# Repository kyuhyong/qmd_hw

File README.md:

# Q_Motor_Driver_hw

A stackable BLDC motor controller board based and compatible with Odrive project (https://github.com/madcowswe/ODriveHardware).

Part of this project is based from azmat's single channel BLDC controller board (https://github.com/azmat-bilal/bldc_motor_controller_pcb.git)

## Introduction

This project includes 3 PCB boards as Main Board(MB), M0 Board(M0B) and M1 Board(M1B). 

- MB : Main controller, USB, CAN interface

- M0B : Gate driver for M0, 5V power supply for MB
- M1B : Gate driver for M1

MB is in between M0B and M1B which are connected by 2mm pitch socket and header. 

If only 1 axis needed the M1B can be removed. 

If more power is needed, simply redesign M0B or M1B with higher power FET's and put together with MB.

## Odrive compatibility

This project is supposed to be compatible with odrive v3.6-56V.

<div align="center">
  
</div>

## Announcement

This project is still in development and need modification to be working as expected.

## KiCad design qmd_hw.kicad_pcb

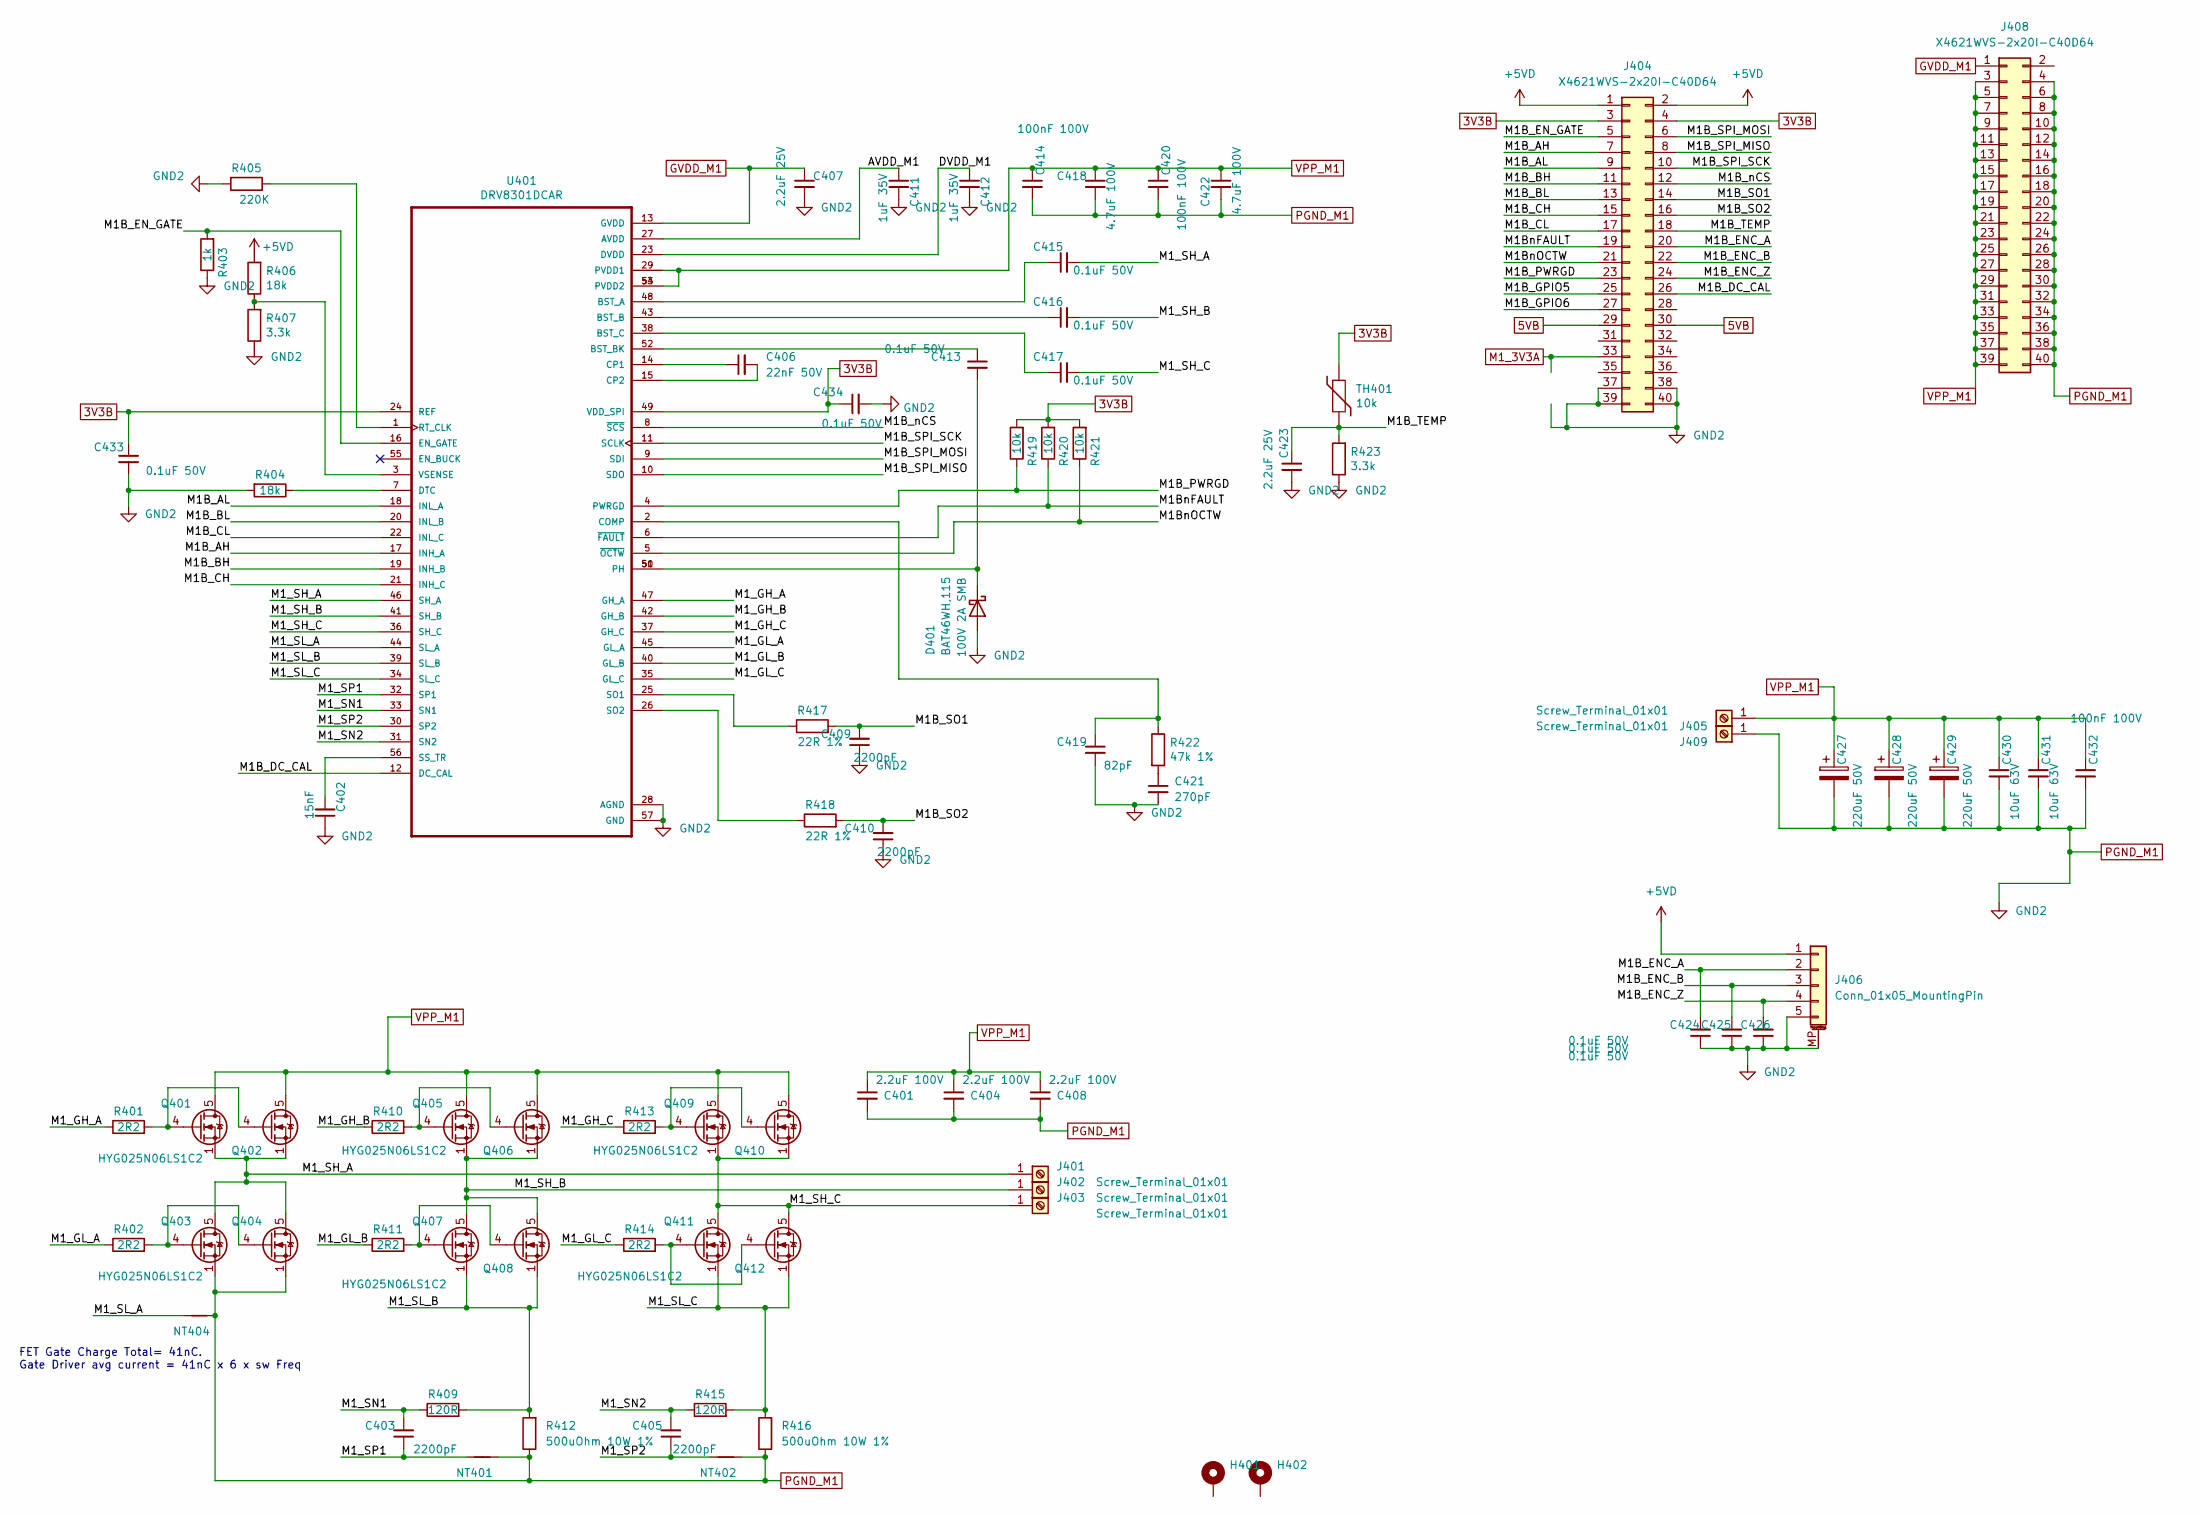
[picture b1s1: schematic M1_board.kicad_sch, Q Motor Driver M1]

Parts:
C401, C404, C408: 2.2uF 100V; C_1210_3225Metric; MPN HMK325B7225KN-T; JLCPN C92775
C402: 15nF; C_0402_1005Metric; MPN GCM155R71E153JA55D
C403, C405, C409, C410: 2200pF; C_0402_1005Metric; MPN CL05B222KB5NNNC; JLCPN C84703
C406: 22nF 50V; C_0402_1005Metric; MPN CL05B223KB5VPNC; JLCPN C307335
C407, C423: 2.2uF 25V; C_0603_1608Metric; MPN CL10A225KB8NNNC; JLCPN C913904
C411, C412: 1uF 35V; C_0603_1608Metric; MPN CL05A105KL5NRNC; JLCPN C307413
C413, C415, C416, C417, C434: 0.1uF 50V; C_0402_1005Metric
C414, C420, C432: 100nF 100V; C_0402_1005Metric; MPN GRM155R62A104KE14D; JLCPN C162178
C418: 4.7uF 100V; C_1210_3225Metric; MPN HMK325C7475KMHPE; JLCPN C385986
C419: 82pF; C_0402_1005Metric; MPN C1005NP0820JGTS; JLCPN C147470
C421: 270pF; C_0603_1608Metric; MPN CGA2B2C0G1H271JT0Y0F; JLCPN C695156
C422: 4.7uF 100V; C_1210_3225Metric; MPN HMK325C7475KN-TE
C424, C425, C426, C433: 0.1uF 50V; C_0603_1608Metric; MPN CL10B104KB8NNNC; JLCPN C1591
C427, C428, C429: 220uF 50V; CP_Elec_10x14.3; MPN EEHZS1H221P; JLCPN C385885
C430, C431: 10uF 63V; C_1210_3225Metric; MPN CL32B106KMVNNWE
D401: 100V 2A SMB; D_SOD-123F; MPN BAT46WH,115; JLCPN C426768
H401: MountingHole_Pad; MountingHole_3.2mm_M3_ISO7380_Pad
H402: MountingHole_Pad; MountingHole_3.2mm_M3_ISO7380_Pad_TopBottom
J401, J402, J403, J405, J409: Screw_Terminal_01x01; SolderWire-2.5sqmm_1x01_D2.4mm_OD3.6mm
J404, J408: X4621WVS-2x20I-C40D64; PinHeader_2x20_P2.0mm_Vertical_SMD_877594051; MPN X4621WVS-2x20I-C40D64; JLCPN C2883178
J406: Conn_01x05_MountingPin; JST_PH_B5B-PH-SM4-TB_1x05-1MP_P2.00mm_Vertical; MPN B5B-PH-SM4-TB(LF)(SN); JLCPN C265085
NT401, NT402, NT404: Net-Tie_2; NetTie-2_SMD_Pad0.5mm
Q401, Q402, Q403, Q404, Q405, Q406, Q407, Q408, Q409, Q410, Q411, Q412: HYG025N06LS1C2; TDSON-8-1; MPN HYG025N06LS1C2
R401, R402, R410, R411, R413, R414: 2R2; R_0603_1608Metric; MPN RC0603FR-072R2L; JLCPN C98220
R403: 1k; R_0402_1005Metric; MPN ERJ-2RKF1001X
R404, R406: 18k; R_0402_1005Metric; MPN CRCW040218K0FKED
R405: 220K; R_0402_1005Metric; MPN CR0402-JW-224GLF; JLCPN C203142
R407, R423: 3.3k; R_0603_1608Metric; MPN RC0603JR-073K3L; JLCPN C114432
R409, R415: 120R; R_0603_1608Metric; MPN ERJ-2RKF1200X
R412, R416: 500uOhm 10W 1%; WSLP3921L5000FEA; MPN WSLP3921L5000FEA
R417, R418: 22R 1%; R_0402_1005Metric; MPN AC0402JR-0722RL; JLCPN C144722
R419, R420, R421: 10k; R_0603_1608Metric; MPN RC0603FR-0710KL
R422: 47k 1%; R_0402_1005Metric; MPN RC0402FR-0747KL; JLCPN C93943
TH401: 10k; R_0402_1005Metric; MPN CRCW040210K0FKEDC
U401: DRV8301DCAR; SOP50P810X120-57N; MPN DRV8301DCAR

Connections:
3V3B: C433.1, C434.1, J404.3, J404.4, R419.2, R420.2, R421.2, TH401.1, U401.24 (REF), U401.49 (VDD_SPI)
5VB: J404.29, J404.30
+5VD: J404.1, J404.2, J406.1, R406.2
/M1_board/AVDD_M1: C411.1, U401.27 (AVDD)
/M1_board/DVDD_M1: C412.1, U401.23 (DVDD)
/M1_board/M1B_AH: J404.7, U401.17 (INH_A)
/M1_board/M1B_AL: J404.9, U401.18 (INL_A)
/M1_board/M1B_BH: J404.11, U401.19 (INH_B)
/M1_board/M1B_BL: J404.13, U401.20 (INL_B)
/M1_board/M1B_CH: J404.15, U401.21 (INH_C)
/M1_board/M1B_CL: J404.17, U401.22 (INL_C)
/M1_board/M1B_DC_CAL: J404.26, U401.12 (DC_CAL)
/M1_board/M1B_ENC_A: C424.2, J404.20, J406.2
/M1_board/M1B_ENC_B: C425.2, J404.22, J406.3
/M1_board/M1B_ENC_Z: C426.2, J404.24, J406.4
/M1_board/M1B_EN_GATE: J404.5, R403.2, U401.16 (EN_GATE)
/M1_board/M1B_GPIO5: J404.25
/M1_board/M1B_GPIO6: J404.27
/M1_board/M1B_PWRGD: J404.23, R419.1, U401.4 (PWRGD)
/M1_board/M1B_SO1: C409.2, J404.14, R417.2
/M1_board/M1B_SO2: C410.2, J404.16, R418.2
/M1_board/M1B_SPI_MISO: J404.8, U401.10 (SDO)
/M1_board/M1B_SPI_MOSI: J404.6, U401.9 (SDI)
/M1_board/M1B_SPI_SCK: J404.10, U401.11 (SCLK)
/M1_board/M1B_TEMP: C423.1, J404.18, R423.2, TH401.2
/M1_board/M1B_nCS: J404.12, U401.8 (~SCS)
/M1_board/M1BnFAULT: J404.19, R420.1, U401.6 (~FAULT)
/M1_board/M1BnOCTW: J404.21, R421.1, U401.5 (~OCTW)
/M1_board/M1_GH_A: R401.1, U401.47 (GH_A)
/M1_board/M1_GH_B: R410.1, U401.42 (GH_B)
/M1_board/M1_GH_C: R413.1, U401.37 (GH_C)
/M1_board/M1_GL_A: R402.1, U401.45 (GL_A)
/M1_board/M1_GL_B: R411.1, U401.40 (GL_B)
/M1_board/M1_GL_C: R414.1, U401.35 (GL_C)
/M1_board/M1_SH_A: C415.2, J401.1, Q401.1 (S), Q401.2 (S), Q401.3 (S), Q402.1 (S), Q402.2 (S), Q402.3 (S), Q403.5 (D), Q404.5 (D), U401.46 (SH_A)
/M1_board/M1_SH_B: C416.2, J402.1, Q405.1 (S), Q405.2 (S), Q405.3 (S), Q406.1 (S), Q406.2 (S), Q406.3 (S), Q407.5 (D), Q408.5 (D), U401.41 (SH_B)
/M1_board/M1_SH_C: C417.2, J403.1, Q409.1 (S), Q409.2 (S), Q409.3 (S), Q410.1 (S), Q410.2 (S), Q410.3 (S), Q411.5 (D), Q412.5 (D), U401.36 (SH_C)
/M1_board/M1_SL_A: NT404.1, U401.44 (SL_A)
/M1_board/M1_SL_B: Q407.1 (S), Q407.2 (S), Q407.3 (S), Q408.1 (S), Q408.2 (S), Q408.3 (S), R409.2, R412.2, U401.39 (SL_B)
/M1_board/M1_SL_C: Q411.1 (S), Q411.2 (S), Q411.3 (S), Q412.1 (S), Q412.2 (S), Q412.3 (S), R415.2, R416.2, U401.34 (SL_C)
/M1_board/M1_SN1: C403.2, R409.1, U401.33 (SN1)
/M1_board/M1_SN2: C405.2, R415.1, U401.31 (SN2)
/M1_board/M1_SP1: C403.1, NT401.1, U401.32 (SP1)
/M1_board/M1_SP2: C405.1, NT402.1, U401.30 (SP2)
GVDD_M1: C407.1, J408.1, U401.13 (GVDD)
M1_3V3A: J404.33
unnamed: C421.1, R422.2
unnamed: C413.2, D401.1 (K), U401.50 (PH), U401.51 (PH)
unnamed: Q401.4 (G), Q402.4 (G), R401.2
unnamed: Q403.4 (G), Q404.4 (G), R402.2
unnamed: Q405.4 (G), Q406.4 (G), R410.2
unnamed: Q407.4 (G), Q408.4 (G), R411.2
unnamed: Q409.4 (G), Q410.4 (G), R413.2
unnamed: Q411.4 (G), Q412.4 (G), R414.2
unnamed: C415.1, U401.48 (BST_A)
unnamed: C416.1, U401.43 (BST_B)
unnamed: C413.1, U401.52 (BST_BK)
unnamed: C417.1, U401.38 (BST_C)
unnamed: C419.1, R422.1, U401.2 (COMP)
unnamed: C406.1, U401.14 (CP1)
unnamed: C406.2, U401.15 (CP2)
unnamed: R404.1, U401.7 (DTC)
unnamed: R405.1, U401.1 (RT_CLK)
unnamed: R417.1, U401.25 (SO1)
unnamed: R418.1, U401.26 (SO2)
unnamed: C402.2, U401.56 (SS_TR)
unnamed: R406.1, R407.2, U401.3 (VSENSE)
PGND_M1: C401.2, C402.1, C404.2, C407.2, C408.2, C409.1, C410.1, C411.2, C412.2, C414.2, C418.2, C419.2, C420.2, C421.2, C422.2, C423.2, C424.1, C425.1, C426.1, C427.2, C428.2, C429.2, C430.2, C431.2, C432.2, C433.2, C434.2, D401.2 (A), J404.37, J404.38, J404.39, J404.40, J406.5, J406.MP (MountPin), J408.4, J408.6, J408.8, J408.10, J408.12, J408.14, J408.16, J408.18, J408.20, J408.22, J408.24, J408.26, J408.28, J408.30, J408.32, J408.34, J408.36, J408.38, J408.40, J409.1, NT401.2, NT402.2, NT404.2, Q403.1 (S), Q403.2 (S), Q403.3 (S), Q404.1 (S), Q404.2 (S), Q404.3 (S), R403.1, R404.2, R405.2, R407.1, R412.1, R416.1, R423.1, U401.28 (AGND), U401.57 (GND)
VPP_M1: C401.1, C404.1, C408.1, C414.1, C418.1, C420.1, C422.1, C427.1, C428.1, C429.1, C430.1, C431.1, C432.1, J405.1, J408.3, J408.5, J408.7, J408.9, J408.11, J408.13, J408.15, J408.17, J408.19, J408.21, J408.23, J408.25, J408.27, J408.29, J408.31, J408.33, J408.35, J408.37, J408.39, Q401.5 (D), Q402.5 (D), Q405.5 (D), Q406.5 (D), Q409.5 (D), Q410.5 (D), U401.29 (PVDD1), U401.53 (PVDD2), U401.54 (PVDD2)

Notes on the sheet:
FET Gate Charge Total= 41nC. Gate Driver avg current = 41nC x 6 x sw Freq

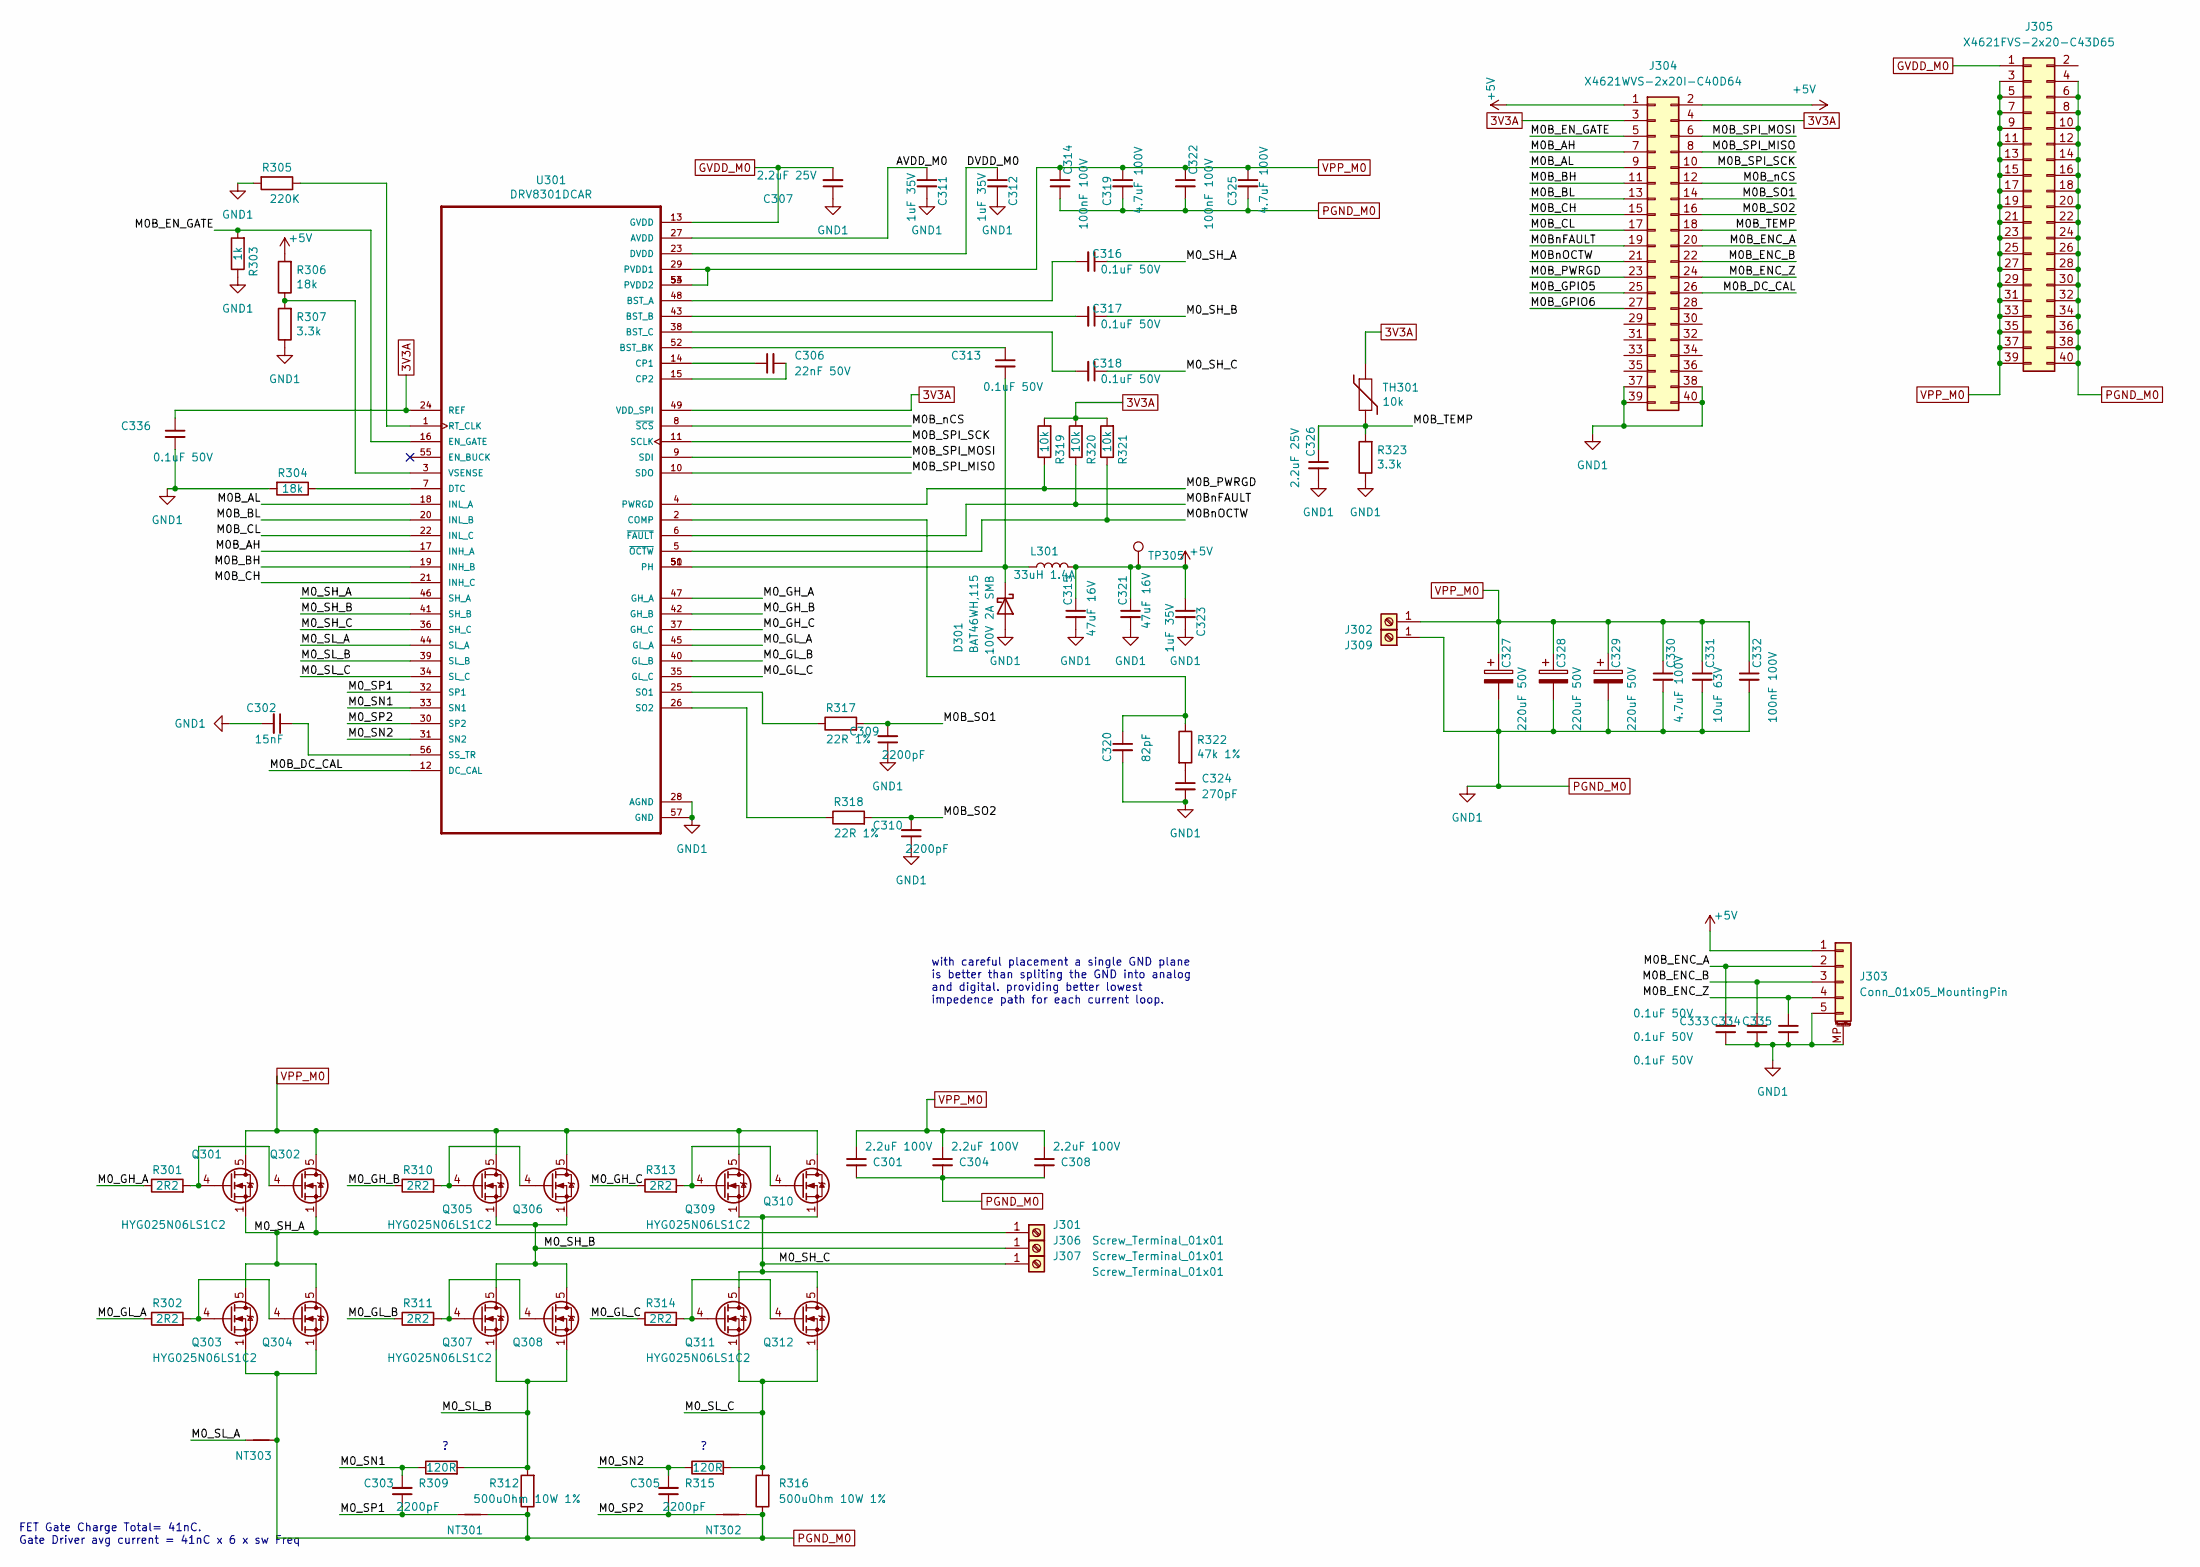
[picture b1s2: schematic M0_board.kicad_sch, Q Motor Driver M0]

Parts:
C301, C304, C308: 2.2uF 100V; C_1210_3225Metric; MPN HMK325B7225KN-T; JLCPN C92775
C302: 15nF; C_0402_1005Metric; MPN GCM155R71E153JA55D
C303, C305, C309, C310: 2200pF; C_0402_1005Metric; MPN CL05B222KB5NNNC; JLCPN C84703
C306: 22nF 50V; C_0402_1005Metric; MPN CL05B223KB5VPNC; JLCPN C307335
C307, C326: 2.2uF 25V; C_0603_1608Metric; MPN CL10A225KB8NNNC; JLCPN C913904
C311, C312, C323: 1uF 35V; C_0603_1608Metric; MPN CL05A105KL5NRNC; JLCPN C307413
C313, C316, C317, C318, C336: 0.1uF 50V; C_0402_1005Metric
C314, C322, C332: 100nF 100V; C_0402_1005Metric; MPN GRM155R62A104KE14D; JLCPN C162178
C315, C321: 47uF 16V; C_1210_3225Metric; MPN GRM32EC81C476KE15L
C319, C325: 4.7uF 100V; C_1210_3225Metric; MPN HMK325C7475KN-TE
C320: 82pF; C_0402_1005Metric; MPN C1005NP0820JGTS; JLCPN C147470
C324: 270pF; C_0603_1608Metric; MPN CGA2B2C0G1H271JT0Y0F; JLCPN C695156
C327, C328, C329: 220uF 50V; CP_Elec_10x14.3; MPN EEHZS1H221P; JLCPN C385885
C330: 4.7uF 100V; C_1210_3225Metric; MPN HMK325C7475KMHPE; JLCPN C385986
C331: 10uF 63V; C_1210_3225Metric; MPN CL32B106KMVNNWE
C333, C334, C335: 0.1uF 50V; C_0603_1608Metric; MPN CL10B104KB8NNNC; JLCPN C1591
D301: 100V 2A SMB; D_SOD-123F; MPN BAT46WH,115; JLCPN C426768
J301, J302, J306, J307, J309: Screw_Terminal_01x01; SolderWire-2.5sqmm_1x01_D2.4mm_OD3.6mm
J303: Conn_01x05_MountingPin; JST_PH_B5B-PH-SM4-TB_1x05-1MP_P2.00mm_Vertical; MPN B5B-PH-SM4-TB(LF)(SN); JLCPN C265085
J304: X4621WVS-2x20I-C40D64; PinHeader_2x20_P2.0mm_Vertical_SMD_877594051; MPN X4621WVS-2x20I-C40D64; JLCPN C2883178
J305: X4621FVS-2x20-C43D65; PinSocket_2x20_P2.00mm_Vertical_SMD; MPN X4621FVS-2x20-C43D65; JLCPN C2883206
L301: 33uH 1.4A; L_Taiyo-Yuden_NR-60xx; MPN NR6045T330M; JLCPN C92942
NT301, NT302, NT303: Net-Tie_2; NetTie-2_SMD_Pad0.5mm
Q301, Q302, Q303, Q304, Q305, Q306, Q307, Q308, Q309, Q310, Q311, Q312: HYG025N06LS1C2; TDSON-8-1; MPN HYG025N06LS1C2
R301, R302, R310, R311, R313, R314: 2R2; R_0603_1608Metric; MPN RC0603FR-072R2L; JLCPN C98220
R303: 1k; R_0402_1005Metric; MPN ERJ-2RKF1001X
R304, R306: 18k; R_0402_1005Metric; MPN CRCW040218K0FKED
R305: 220K; R_0402_1005Metric; MPN CR0402-JW-224GLF; JLCPN C203142
R307, R323: 3.3k; R_0603_1608Metric; MPN RC0603JR-073K3L; JLCPN C114432
R309, R315: 120R; R_0603_1608Metric; MPN ERJ-2RKF1200X
R312, R316: 500uOhm 10W 1%; WSLP3921L5000FEA; MPN WSLP3921L5000FEA
R317, R318: 22R 1%; R_0402_1005Metric; MPN AC0402JR-0722RL; JLCPN C144722
R319, R320, R321: 10k; R_0603_1608Metric; MPN RC0603FR-0710KL
R322: 47k 1%; R_0402_1005Metric; MPN RC0402FR-0747KL; JLCPN C93943
TH301: 10k; R_0402_1005Metric; MPN CRCW040210K0FKEDC
TP305: TestPoint; TestPoint_Pad_D1.5mm
U301: DRV8301DCAR; SOP50P810X120-57N; MPN DRV8301DCAR

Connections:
3V3A: C336.1, J304.3, J304.4, R319.2, R320.2, R321.2, TH301.1, U301.24 (REF), U301.49 (VDD_SPI)
+5V: C315.1, C321.1, C323.1, J303.1, J304.1, J304.2, L301.2, R306.2, TP305.1
/M0_board/AVDD_M0: C311.1, U301.27 (AVDD)
/M0_board/DVDD_M0: C312.1, U301.23 (DVDD)
/M0_board/M0B_AH: J304.7, U301.17 (INH_A)
/M0_board/M0B_AL: J304.9, U301.18 (INL_A)
/M0_board/M0B_BH: J304.11, U301.19 (INH_B)
/M0_board/M0B_BL: J304.13, U301.20 (INL_B)
/M0_board/M0B_CH: J304.15, U301.21 (INH_C)
/M0_board/M0B_CL: J304.17, U301.22 (INL_C)
/M0_board/M0B_DC_CAL: J304.26, U301.12 (DC_CAL)
/M0_board/M0B_ENC_A: C333.1, J303.2, J304.20
/M0_board/M0B_ENC_B: C334.1, J303.3, J304.22
/M0_board/M0B_ENC_Z: C335.1, J303.4, J304.24
/M0_board/M0B_EN_GATE: J304.5, R303.2, U301.16 (EN_GATE)
/M0_board/M0B_GPIO5: J304.25
/M0_board/M0B_GPIO6: J304.27
/M0_board/M0B_PWRGD: J304.23, R319.1, U301.4 (PWRGD)
/M0_board/M0B_SO1: C309.2, J304.14, R317.2
/M0_board/M0B_SO2: C310.2, J304.16, R318.2
/M0_board/M0B_SPI_MISO: J304.8, U301.10 (SDO)
/M0_board/M0B_SPI_MOSI: J304.6, U301.9 (SDI)
/M0_board/M0B_SPI_SCK: J304.10, U301.11 (SCLK)
/M0_board/M0B_TEMP: C326.1, J304.18, R323.2, TH301.2
/M0_board/M0B_nCS: J304.12, U301.8 (~SCS)
/M0_board/M0BnFAULT: J304.19, R320.1, U301.6 (~FAULT)
/M0_board/M0BnOCTW: J304.21, R321.1, U301.5 (~OCTW)
/M0_board/M0_GH_A: R301.1, U301.47 (GH_A)
/M0_board/M0_GH_B: R310.1, U301.42 (GH_B)
/M0_board/M0_GH_C: R313.1, U301.37 (GH_C)
/M0_board/M0_GL_A: R302.1, U301.45 (GL_A)
/M0_board/M0_GL_B: R311.1, U301.40 (GL_B)
/M0_board/M0_GL_C: R314.1, U301.35 (GL_C)
/M0_board/M0_SH_A: C316.1, J301.1, Q301.1 (S), Q301.2 (S), Q301.3 (S), Q302.1 (S), Q302.2 (S), Q302.3 (S), Q303.5 (D), Q304.5 (D), U301.46 (SH_A)
/M0_board/M0_SH_B: C317.1, J306.1, Q305.1 (S), Q305.2 (S), Q305.3 (S), Q306.1 (S), Q306.2 (S), Q306.3 (S), Q307.5 (D), Q308.5 (D), U301.41 (SH_B)
/M0_board/M0_SH_C: C318.1, J307.1, Q309.1 (S), Q309.2 (S), Q309.3 (S), Q310.1 (S), Q310.2 (S), Q310.3 (S), Q311.5 (D), Q312.5 (D), U301.36 (SH_C)
/M0_board/M0_SL_A: NT303.1, U301.44 (SL_A)
/M0_board/M0_SL_B: Q307.1 (S), Q307.2 (S), Q307.3 (S), Q308.1 (S), Q308.2 (S), Q308.3 (S), R309.2, R312.2, U301.39 (SL_B)
/M0_board/M0_SL_C: Q311.1 (S), Q311.2 (S), Q311.3 (S), Q312.1 (S), Q312.2 (S), Q312.3 (S), R315.2, R316.2, U301.34 (SL_C)
/M0_board/M0_SN1: C303.2, R309.1, U301.33 (SN1)
/M0_board/M0_SN2: C305.2, R315.1, U301.31 (SN2)
/M0_board/M0_SP1: C303.1, NT301.1, U301.32 (SP1)
/M0_board/M0_SP2: C305.1, NT302.1, U301.30 (SP2)
GVDD_M0: C307.2, J305.1, U301.13 (GVDD)
unnamed: C324.1, R322.2
unnamed: C313.2, D301.1 (K), L301.1, U301.50 (PH), U301.51 (PH)
unnamed: Q301.4 (G), Q302.4 (G), R301.2
unnamed: Q303.4 (G), Q304.4 (G), R302.2
unnamed: Q305.4 (G), Q306.4 (G), R310.2
unnamed: Q307.4 (G), Q308.4 (G), R311.2
unnamed: Q309.4 (G), Q310.4 (G), R313.2
unnamed: Q311.4 (G), Q312.4 (G), R314.2
unnamed: C316.2, U301.48 (BST_A)
unnamed: C317.2, U301.43 (BST_B)
unnamed: C313.1, U301.52 (BST_BK)
unnamed: C318.2, U301.38 (BST_C)
unnamed: C320.1, R322.1, U301.2 (COMP)
unnamed: C306.1, U301.14 (CP1)
unnamed: C306.2, U301.15 (CP2)
unnamed: R304.1, U301.7 (DTC)
unnamed: R305.1, U301.1 (RT_CLK)
unnamed: R317.1, U301.25 (SO1)
unnamed: R318.1, U301.26 (SO2)
unnamed: C302.1, U301.56 (SS_TR)
unnamed: R306.1, R307.2, U301.3 (VSENSE)
PGND_M0: C301.2, C302.2, C304.2, C307.1, C308.2, C309.1, C310.1, C311.2, C312.2, C314.2, C315.2, C319.2, C320.2, C321.2, C322.2, C323.2, C324.2, C325.2, C326.2, C327.2, C328.2, C329.2, C330.2, C331.2, C332.2, C333.2, C334.2, C335.2, C336.2, D301.2 (A), J303.5, J303.MP (MountPin), J304.37, J304.38, J304.39, J304.40, J305.4, J305.6, J305.8, J305.10, J305.12, J305.14, J305.16, J305.18, J305.20, J305.22, J305.24, J305.26, J305.28, J305.30, J305.32, J305.34, J305.36, J305.38, J305.40, J309.1, NT301.2, NT302.2, NT303.2, Q303.1 (S), Q303.2 (S), Q303.3 (S), Q304.1 (S), Q304.2 (S), Q304.3 (S), R303.1, R304.2, R305.2, R307.1, R312.1, R316.1, R323.1, U301.28 (AGND), U301.57 (GND)
VPP_M0: C301.1, C304.1, C308.1, C314.1, C319.1, C322.1, C325.1, C327.1, C328.1, C329.1, C330.1, C331.1, C332.1, J302.1, J305.3, J305.5, J305.7, J305.9, J305.11, J305.13, J305.15, J305.17, J305.19, J305.21, J305.23, J305.25, J305.27, J305.29, J305.31, J305.33, J305.35, J305.37, J305.39, Q301.5 (D), Q302.5 (D), Q305.5 (D), Q306.5 (D), Q309.5 (D), Q310.5 (D), U301.29 (PVDD1), U301.53 (PVDD2), U301.54 (PVDD2)

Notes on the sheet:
with careful placement a single GND plane is better than spliting the GND into analog and digital. providing better lowest impedence path for each current loop.
FET Gate Charge Total= 41nC. Gate Driver avg current = 41nC x 6 x sw Freq
